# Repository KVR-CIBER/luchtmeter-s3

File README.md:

# Luchtmeter S3 (v2.0)

By **Kobe Vanrobaeys** ([@KVR-CIBER](https://github.com/KVR-CIBER)) and co-inventor **[@varol56](https://github.com/varol56)**.

ESP32-S3 air-quality meter behind a **4.3" 800x480 IPS capacitive touchscreen**, LiPo battery, deep sleep, NFC tag and
Home Assistant (ESPHome). The front is only the screen, a small light window and the NFC spot; every part sits on the back.

| Block | Part |
|---|---|
| Brain | **ESP32-S3-WROOM-1U-N16R8**: external 2.4 GHz antenna (U.FL) at the top of the case, the best WiFi possible |
| Screen | **Waveshare 4.3inch Capacitive Touch LCD** (art. 16249, IPS 800x480, GT911): screwed (M2) onto its own 4.1 mm standoffs; 40-pin FFC to J1 |
| CO2 | Sensirion **SCD41** (photoacoustic, 400-5000 ppm), behind the back vents |
| Temperature / humidity | Sensirion **SHT45** (+-0.1 C) on a slotted, copper-free tongue (no heat from the ESP/charger) |
| Light | **LTR-303ALS** on the front, behind a light pipe in the case |
| NFC | **ST25DV04K** + 8-turn antenna coil on the board (3.5 uH + 10 pF). A phone tap can wake the meter (GPO -> IO16) |
| Charging | TI **BQ24075**, ~250 mA for the 300 mAh LiPo (R5 3.6k), power path: works while charging. Red LED = charging, green = USB |
| Battery | LiPo soldered to **BAT+ / BAT-**, extra DW01A protection |
| 3.3 V / 5 V | XC6220 LDO (8 uA) / TPS61023 boost for the screen (off in deep sleep) |
| Test points | **TP1-TP13** on the back, 1.5 mm pads in one row with the net name in silkscreen: GND, VBUS, VBAT, VSYS, 3V3, 3V3_SW, V5D, TP_3V3, SDA0, SCL0, SDA1, SCL1, GND (issue #1) |
| Probe connector | **J3** (1x4, 2.54 mm, not assembled) at the left edge next to the USB-C: GND / 3V3 / SDA1 / SCL1 (Qwiic order) on the second I2C bus, for an external SHT4x probe (issue #2). 3V3 = TP_3V3, the screen's 3.3 V, the same rail as the I2C1 pull-ups |

Board 106 x 88 mm, 4 layers, notch on the right for the screen's 2x20 header. Checks: **DRC 0, unconnected 0, ERC 0, parity 0**.
(All routed by the tools: Freerouting + `tools/finisher.py`. Freerouting runs multithreaded and is not deterministic;
if `build_all.sh` ends with open connections, run it again.)

## Check before ordering
1. **FFC cable** between the screen (H1) and J1: J1 is turned so pin 1 is on the same side as on the screen; the cable makes
   a U-fold. Check with the cable that comes with the screen (same-side or opposite-side contacts) before soldering.
2. **NFC tuning**: C23 = 10 pF is calculated; the best value can be 8-15 pF (test with the ST "NFC Tap" app).

## Probe on J3 (issue #2)
J3 is on the touch bus (I2C1, GPIO7/8, GT911 at 0x5D) and not on the sensor bus, because an SHT45 probe has the same fixed
address (0x44) as U6. Its 3V3 pin is the screen's own 3.3 V (TP_3V3), so the probe is only powered while the screen is on,
and a powered-down probe is never fed through SDA/SCL. Solder the 4 wires straight onto J3 (a standard 8.5 mm header would
touch the back plate) and lay the cable into the notch in the left wall of the case. Firmware: uncomment the `sht4x`
block on `bus_touch` in `firmware/luchtmeter.yaml`.

## Case (`case/`)
`build_case.py` (CadQuery) -> `case/out/`: `luchtmeter_voorkant.stl` (print face-down), `luchtmeter_achterplaat.stl`,
`luchtmeter_standaard.stl` (desk stand, 20 deg), STEP files, and photo renders (`foto_*.png`, KiCad raytracer).
111.6 x 93.6 x 25.6 mm. 2x M3 x 12 self-tapping screws hold back plate + PCB; 4x M2 x 5 screws hold the PCB to the screen.
The left wall has the USB-C opening and a 5 mm cable notch for the probe on J3 (`render_linkerwand.png`). `render.py`
(trimesh + matplotlib + networkx) makes the shaded case renders.

## Firmware
`firmware/luchtmeter.yaml` (ESPHome, not yet tested on hardware; `esphome config` + `esphome compile` ok with ESPHome
2026.10.0): RGB565 screen (rpi_dpi_rgb), GT911 touch, SCD41 single-shot, SHT45, LTR-303, battery %, deep sleep 5 min,
wake on WEKKEN button or NFC tap. Before 3V3_SW (GPIO15) or the screen (GPIO17) goes off, the SDA/SCL pins of that bus
(GPIO4/5, GPIO7/8) become inputs without pull-up, so the ESP32 never feeds the powered-down chips through its I/O pins;
the ESP32's internal I2C pull-ups are off (the 4k7 pull-ups on the board are on the switched rails). Optional: external
SHT4x probe on J3 (commented out). Needs a `firmware/secrets.yaml` with `wifi_ssid` / `wifi_password`.

## Files
`tools/design.py` = single source of truth; `tools/build_all.sh` rebuilds everything. JLC files in `fab/`.

## Build environment
The board files are **KiCad 10**. Tool paths come from `tools/env.sh` / `tools/kienv.py`: on macOS the defaults are
KiCad.app and brew's openjdk, anything can be overridden with `KICAD_PY`, `KICAD_CLI`, `KICAD_SHARE`, `VENV_PY`, `JAVA`.

Linux (tested on Debian 13 trixie, which only ships KiCad 9):
```sh
apt install flatpak openjdk-25-jre-headless python3-venv          # freerouting 2.4.1 needs Java 25
flatpak remote-add --if-not-exists flathub https://dl.flathub.org/repo/flathub.flatpakrepo
flatpak install flathub org.kicad.KiCad                            # KiCad 10; tools/flatpak/ wraps kicad-cli + its python
# default global library tables (normally made on the first GUI start; without them ERC warns about 'power')
flatpak run --command=sh org.kicad.KiCad -c 'cp -n /app/extensions/Library/template/*-lib-table $XDG_CONFIG_HOME/kicad/10.0/'
python3 -m venv .venv && .venv/bin/pip install numpy shapely matplotlib cadquery trimesh networkx
python3 -m venv .venv-esphome && .venv-esphome/bin/pip install esphome
tools/build_all.sh                                                 # board + schematic + routing + checks + fab/
.venv/bin/python case/build_case.py && .venv/bin/python case/render.py
cd firmware && ../.venv-esphome/bin/esphome compile luchtmeter.yaml
```
The flatpak sandbox has its own `/tmp`: give kicad-cli output paths inside the repo.

## Authors
- Kobe Vanrobaeys ([@KVR-CIBER](https://github.com/KVR-CIBER))
- [@varol56](https://github.com/varol56), co-inventor

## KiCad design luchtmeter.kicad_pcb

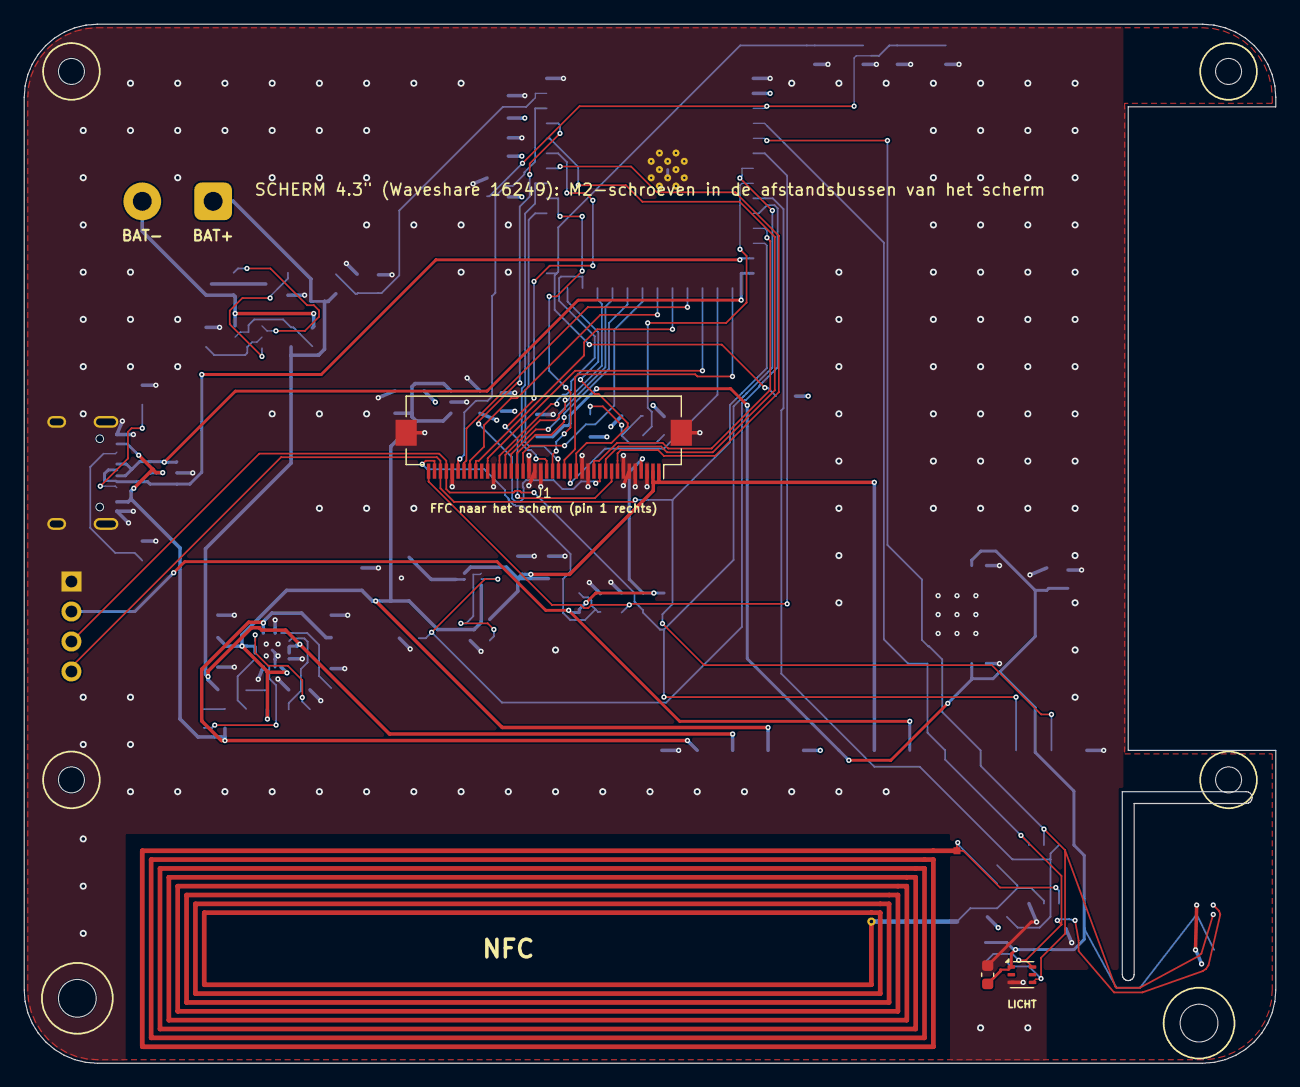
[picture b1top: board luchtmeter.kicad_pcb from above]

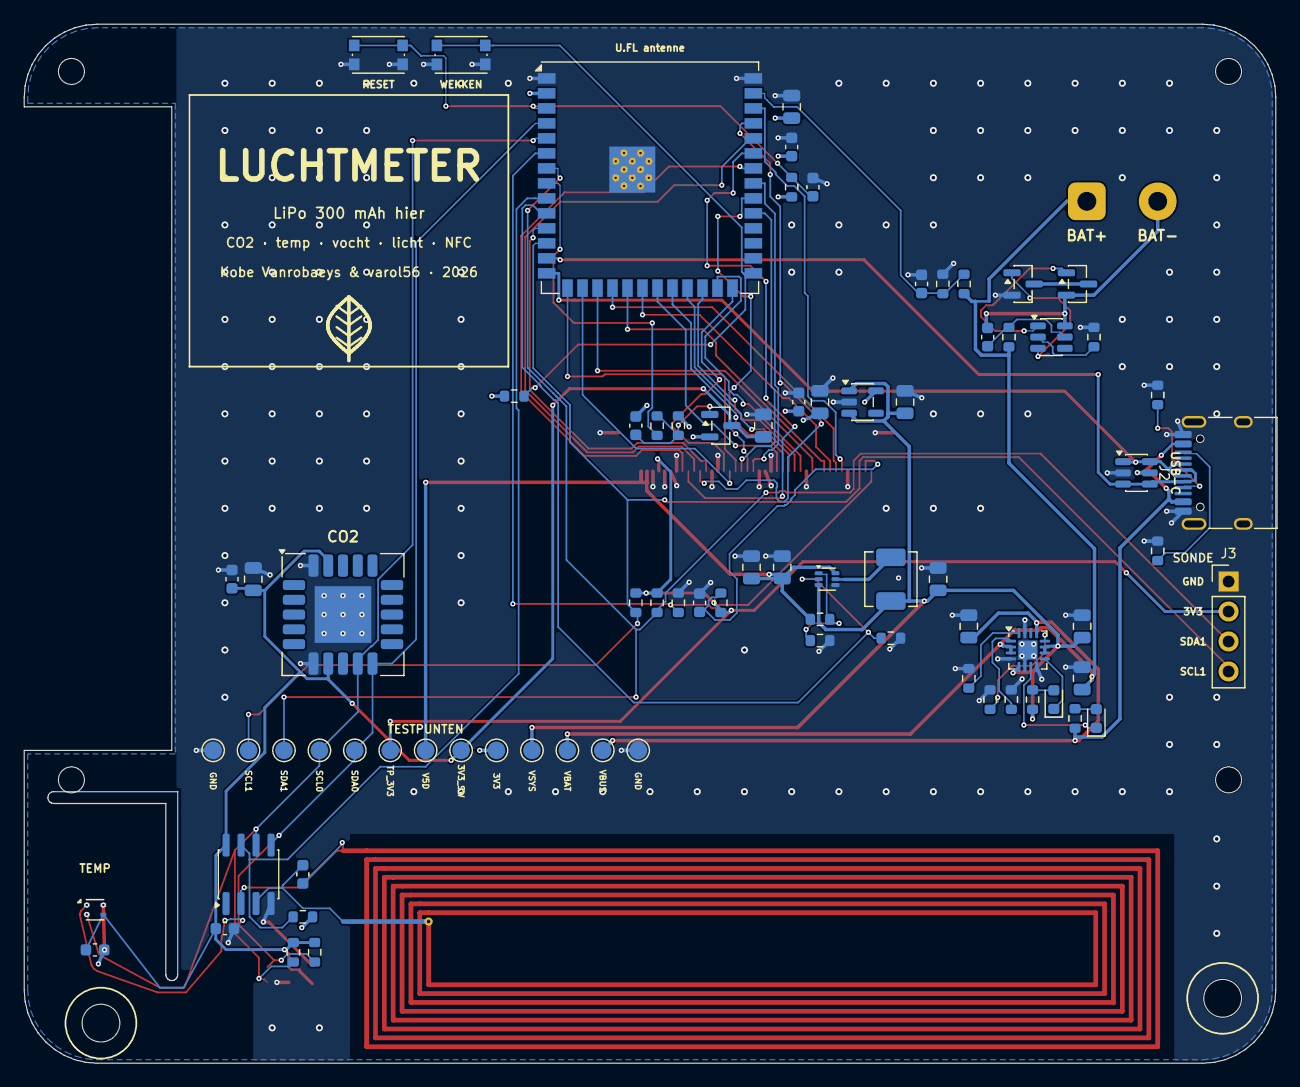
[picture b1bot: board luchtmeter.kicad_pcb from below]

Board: 4 copper layers, 106.0 x 88.0 mm, 90 parts (80 on the bottom side), 63 nets.

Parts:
ANT1: NFC antenne; NFC_Coil
C1, C10, C15, C16: 22u; C_0805_2012Metric
C2, C7, C8, C11, C18, C20, C21, C22: 100n; C_0603_1608Metric
C3, C17: 1u; C_0603_1608Metric
C4, C6: 4u7; C_0805_2012Metric
C5, C9, C13, C14, C19: 10u; C_0805_2012Metric
C12: 47n; C_0603_1608Metric
C23: 10p; C_0603_1608Metric
D1: rood laden; LED_0603_1608Metric
D2: groen USB; LED_0603_1608Metric
H1, H2, H3, H4: M2; MountingHole_2.2mm_M2
H5, H6: M3; MountingHole_3.2mm_M3
J1: SCHERM; Hirose_FH12-40S-0.5SH_1x40-1MP_P0.50mm_Horizontal
J2: USB-C; USB_C_Receptacle_HRO_TYPE-C-31-M-12
J3: SONDE I2C1; PinHeader_1x04_P2.54mm_Vertical
J4: BATTERIJ; SolderWire_2pad_P6mm_D1.6mm_BAT
L1: 1uH; L_Sunlord_MWSA0402S
Q2: AO3401A; SOT-23
Q3, Q4: AO3400A; SOT-23
R1, R2, R7, R15, R19, R20: 10k; R_0603_1608Metric
R3, R4: 5k1; R_0603_1608Metric
R5: 3.6k; R_0603_1608Metric
R6: 1.1k; R_0603_1608Metric
R8, R9, R11: 1k; R_0603_1608Metric
R10: 100; R_0603_1608Metric
R12, R13: 1M; R_0603_1608Metric
R14, R17, R18, R25: 100k; R_0603_1608Metric
R16: 732k; R_0603_1608Metric
R21, R22, R23, R24: 4k7; R_0603_1608Metric
SW1: WEKKEN; SW_Push_1P1T_NO_CK_KMR2
SW2: RESET; SW_Push_1P1T_NO_CK_KMR2
TP1, TP13: GND; TestPoint_Pad_D1.5mm
TP2: VBUS; TestPoint_Pad_D1.5mm
TP3: VBAT; TestPoint_Pad_D1.5mm
TP4: VSYS; TestPoint_Pad_D1.5mm
TP5: 3V3; TestPoint_Pad_D1.5mm
TP6: 3V3_SW; TestPoint_Pad_D1.5mm
TP7: V5D; TestPoint_Pad_D1.5mm
TP8: TP_3V3; TestPoint_Pad_D1.5mm
TP9: SDA0; TestPoint_Pad_D1.5mm
TP10: SCL0; TestPoint_Pad_D1.5mm
TP11: SDA1; TestPoint_Pad_D1.5mm
TP12: SCL1; TestPoint_Pad_D1.5mm
U1: ESP32-S3-WROOM-1U-N16R8; ESP32-S3-WROOM-1U
U2: USBLC6-2SC6; SOT-23-6
U3: XC6220B331MR; SOT-23-5
U4: LTR-303ALS-01; Lite-On_LTR-303ALS-01
U5: SCD41-D-R2; Sensirion_SCD4x-1EP_10.1x10.1mm_P1.25mm_EP4.8x4.8mm
U6: SHT45; Sensirion_DFN-4_1.5x1.5mm_P0.8mm_SHT4x_NoCentralPad
U7: BQ24075; VQFN-16-1EP_3x3mm_P0.5mm_EP1.6x1.6mm
U8: DW01A; SOT-23-6
U9: TPS61023; SOT-563
U10: ST25DV04K; SOIC-8_3.9x4.9mm_P1.27mm

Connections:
3V3: C1.1, C2.1, C10.1, C11.1, C12.2, Q2.2, R1.1, R2.1, R14.2, R25.2, TP5.1, U1.2, U3.5
3V3_SW: C13.1, C18.1, C19.1, C20.1, C21.1, C22.1, Q2.3, R23.2, R24.2, TP6.1, U4.1, U5.7, U5.19, U6.3, U10.8
BATN: C7.2, J4.2, Q3.2, U8.6
BAT_MID: Q3.3, Q4.3
BL_PWM: J1.35, U1.38
BST_FB: R16.2, R17.1, U9.1
BST_SW: L1.2, U9.5
CC1: J2.A5, R3.1
CC2: J2.B5, R4.1
CHG: D1.1, U7.9
CH_ILIM: R6.1, U7.12
CH_ISET: R5.1, U7.16
CH_TS: R7.1, U7.1
DE: J1.34, U1.18
DISP_ON: R18.1, U1.10, U9.2
DW_CS: R11.1, U8.2
DW_OC: Q4.1, U8.3
DW_OD: Q3.1, U8.1
DW_VCC: C7.1, R10.2, U8.5
ESP_EN: C3.1, R1.2, SW2.1, U1.3
ESP_IO0: R2.2, SW1.1, U1.27
GND: C1.2, C2.2, C3.2, C4.2, C5.2, C6.2, C8.2, C9.2, C10.2, C11.2, C13.2, C14.2, C15.2, C16.2, C17.2, C18.2, C19.2, C20.2, C21.2, C22.2, J1.3, J1.5, J1.6, J1.7, J1.13, J1.14, J1.21, J1.22, J1.23, J1.29, J1.36, J1.MP, J2.A1, J2.A12, J2.B1, J2.B12, J2.SH, J3.1, Q4.2, R3.2, R4.2, R5.2, R6.2, R7.2, R11.2, R13.2, R17.2, R18.2, R20.2, SW1.2, SW2.2, TP1.1, TP13.1, U1.1, U1.40, U1.41, U2.2, U3.2, U4.3, U5.6, U5.20, U5.21, U6.4, U7.4, U7.6, U7.8, U7.15, U7.17, U9.4, U10.4
HSYNC: J1.32, U1.19
LCD_B3: J1.24, U1.21
LCD_B4: J1.25, U1.22
LCD_B5: J1.26, U1.23
LCD_B6: J1.27, U1.24
LCD_B7: J1.28, U1.25
LCD_G2: J1.15, U1.26
LCD_G3: J1.16, U1.16
LCD_G4: J1.17, U1.15
LCD_G5: J1.18, U1.31
LCD_G6: J1.19, U1.32
LCD_G7: J1.20, U1.33
LCD_R3: J1.8, U1.34
LCD_R4: J1.9, U1.35
LCD_R5: J1.10, U1.36
LCD_R6: J1.11, U1.37
LCD_R7: J1.12, U1.11
LED_CHG_A: D1.2, R8.2
LED_PG_A: D2.2, R9.2
NFC_AC0: ANT1.1, C23.1, U10.2
NFC_AC1: ANT1.2, C23.2, U10.3
NFC_GPO: R25.1, U1.9, U10.7
PCLK: J1.30, U1.17
PGOOD: D2.1, U7.7
PWR_EN: R15.1, U1.8
PWR_G: C12.1, Q2.1, R14.1, R15.2
SCL0: R24.1, TP10.1, U1.5, U4.4, U5.9, U6.2, U10.6
SCL1: J1.38, J3.4, R22.1, TP12.1, U1.12
SDA0: R23.1, TP9.1, U1.4, U4.6, U5.10, U6.1, U10.5
SDA1: J1.37, J3.3, R21.1, TP11.1, U1.7
TP_3V3: J1.4, J3.2, R19.1, R21.2, R22.2, TP8.1
TP_INT: J1.40, R20.1, U1.6
TP_RST: C17.1, J1.39, R19.2
USB_DM: J2.A7, J2.B7, U1.13, U2.3, U2.4
USB_DP: J2.A6, J2.B6, U1.14, U2.1, U2.6
V5D: C15.1, C16.1, J1.1, J1.2, R16.1, TP7.1, U9.6
VBAT: C6.1, J4.1, R10.1, R12.1, TP3.1, U7.2, U7.3
VBAT_SENSE: C8.1, R12.2, R13.1, U1.39
VBUS: C4.1, J2.A4, J2.A9, J2.B4, J2.B9, R9.1, TP2.1, U2.5, U7.13
VSYNC: J1.33, U1.20
VSYS: C5.1, C9.1, C14.1, L1.1, R8.1, TP4.1, U3.1, U3.3, U7.5, U7.10, U7.11, U9.3

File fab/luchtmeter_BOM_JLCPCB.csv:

Comment,Designator,Footprint,Quantity,MPN / note,LCSC Part #
ESP32-S3-WROOM-1U-N16R8,U1,ESP32-S3-WROOM-1U,1,ESP32-S3-WROOM-1U-N16R8 (U.FL; use a 2.4 GHz flex/dipole antenna at the top of the case),C3013946
22u,"C1,C10,C15,C16",C_0805_2012Metric,4,0805 22u X5R ceramic,C29277
100n,"C2,C7,C8,C11,C18,C20,C21,C22",C_0603_1608Metric,8,0603 100n X7R ceramic,C14663
10k,"R1,R2,R15",R_0603_1608Metric,3,0603 10k 1%,C25804
1u,"C3,C17",C_0603_1608Metric,2,0603 1u X5R ceramic,C15849
WEKKEN,SW1,SW_Push_1P1T_NO_CK_KMR2,1,CK KMR221G: wake from deep sleep (= BOOT when held at reset),C72443
RESET,SW2,SW_Push_1P1T_NO_CK_KMR2,1,CK KMR221G,C72443
USB-C,J2,USB_C_Receptacle_HRO_TYPE-C-31-M-12,1,HRO TYPE-C-31-M-12,C165948
5k1,"R3,R4",R_0603_1608Metric,2,0603 5k1 1%,C23186
USBLC6-2SC6,U2,SOT-23-6,1,USBLC6-2SC6,C2687116
BQ24075,U7,VQFN-16-1EP_3x3mm_P0.5mm_EP1.6x1.6mm,1,TI BQ24075RGTR (Li-ion charger + power path),C15464
4u7,"C4,C6",C_0805_2012Metric,2,0805 4u7 X5R ceramic,C132173
10u,"C5,C9,C13,C14,C19",C_0805_2012Metric,5,0805 10u X5R ceramic,C15850
3.6k,R5,R_0603_1608Metric,1,0603 3.6k 1% (charge ~250 mA; 1k = 0.9 A),C22980
1.1k,R6,R_0603_1608Metric,1,0603 1.1k 1% (input limit ~1.4 A),C22764
10k,R7,R_0603_1608Metric,1,"0603 10k 1% (TS: fixed 10k, no NTC)",C25804
1k,"R8,R9,R11",R_0603_1608Metric,3,0603 1k 1%,C21190
rood laden,D1,LED_0603_1608Metric,1,LED 0603 red (charging),C2286
groen USB,D2,LED_0603_1608Metric,1,LED 0603 green (USB power),C12624
BATTERIJ,J4,SolderWire_2pad_P6mm_D1.6mm_BAT,1,solder pads for the LiPo leads,"(solder pads, no part)"
DW01A,U8,SOT-23-6,1,DW01A (Li-ion protection),C351410
100,R10,R_0603_1608Metric,1,0603 100 1%,C22775
AO3400A,Q3,SOT-23,1,AO3400A (discharge FET),C20917
AO3400A,Q4,SOT-23,1,AO3400A (charge FET),C20917
1M,R12,R_0603_1608Metric,1,0603 1M 1% (battery voltage / 2),C22935
1M,R13,R_0603_1608Metric,1,0603 1M 1%,C22935
XC6220B331MR,U3,SOT-23-5,1,Torex XC6220B331MR-G,C86534
AO3401A,Q2,SOT-23,1,AO3401A (load switch: sensors + NFC),C15127
100k,"R14,R17,R25",R_0603_1608Metric,3,0603 100k 1%,C25803
47n,C12,C_0603_1608Metric,1,0603 47n X7R ceramic,C107093
TPS61023,U9,SOT-563,1,"TI TPS61023DRLR (3.7 A boost, 0.1 uA shutdown)",C919459
1uH,L1,L_Sunlord_MWSA0402S,1,Sunlord MWSA0402S-1R0MT (1 uH),C408332
732k,R16,R_0603_1608Metric,1,0603 732k 1%,C23239
100k,R18,R_0603_1608Metric,1,0603 100k (screen off at boot / in sleep),C25803
SCHERM,J1,Hirose_FH12-40S-0.5SH_1x40-1MP_P0.50mm_Horizontal,1,Hirose FH12-40S-0.5SH(55): 40-pin 0.5 mm FFC to the Waveshare 4.3in Capacitive Touch LCD (RGB cable interface),C202114
10k,R19,R_0603_1608Metric,1,0603 10k (GT911 power-on reset),C25804
10k,R20,R_0603_1608Metric,1,0603 10k (INT low at reset -> GT911 address 0x5D),C25804
4k7,"R21,R22,R23,R24",R_0603_1608Metric,4,0603 4k7 1%,C23162
LTR-303ALS-01,U4,Lite-On_LTR-303ALS-01,1,"LTR-303ALS-01 (ambient light, front window)",C364577
SCD41-D-R2,U5,Sensirion_SCD4x-1EP_10.1x10.1mm_P1.25mm_EP4.8x4.8mm,1,"Sensirion SCD41-D-R2 (CO2 400-5000 ppm + RH/T), behind the back vents",C3659294
SHT45,U6,Sensirion_DFN-4_1.5x1.5mm_P0.8mm_SHT4x_NoCentralPad,1,Sensirion SHT45-AD1B-R2 (+-0.1 C),C5221601
ST25DV04K,U10,SOIC-8_3.9x4.9mm_P1.27mm,1,"ST ST25DV04K-IER6S3 (dynamic NFC tag, I2C)",C155601
NFC antenne,ANT1,NFC_Coil,1,"PCB loop antenna (copper on the board, no part)","(PCB copper, no part)"
10p,C23,C_0603_1608Metric,1,0603 10p C0G (3.5 uH coil + 28.5 pF internal + 10 pF = 13.6 MHz; tune 8-15 pF),C1634

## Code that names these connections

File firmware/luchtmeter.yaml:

# Luchtmeter S3 v2 - ESPHome firmware for Home Assistant (first version, NOT yet tested on hardware)
# Authors: Kobe Vanrobaeys (@KVR-CIBER) & varol56 (@varol56, co-inventor)
# Screen: Waveshare 4.3in Capacitive Touch LCD (800x480 RGB565 + GT911). Sensors: SCD41, SHT45, LTR-303. NFC: ST25DV04K.
# Battery: wakes every 5 min (or on the WEKKEN button / an NFC tap), measures, sends to Home Assistant, sleeps again.

substitutions:
  name: luchtmeter
  sleep_time: 5min
  awake_time: 45s

esphome:
  name: ${name}
  friendly_name: Luchtmeter
  platformio_options:
    board_build.flash_mode: dio
  on_boot:
    - priority: 1100                           # before the I2C buses are set up (priority 1000)
      then:
        - lambda: |-
            // the I2C pins were held as floating inputs through deep sleep (release_*_bus): give them back
            for (gpio_num_t p : {GPIO_NUM_4, GPIO_NUM_5, GPIO_NUM_7, GPIO_NUM_8}) gpio_hold_dis(p);
    - priority: 900
      then:
        - switch.turn_on: sensor_power         # 3V3_SW: sensors + NFC
        - switch.turn_on: screen_power         # 5 V boost for the screen
  on_shutdown:                                 # before deep sleep: screen off first, then the sensor rail
    - light.turn_off: backlight
    - switch.turn_off: screen_power
    - switch.turn_off: sensor_power

esp32:
  board: esp32-s3-devkitc-1
  variant: esp32s3
  flash_size: 16MB
  framework:
    type: esp-idf

psram:
  mode: octal
  speed: 80MHz

wifi:                                          # WROOM-1U + external antenna at the top of the case
  ssid: !secret wifi_ssid
  password: !secret wifi_password
  fast_connect: true

api:
ota:
  - platform: esphome
logger:

# ---------------------------------------------------------------- power + sleep
# Issue #2 (varol56): the I2C pull-ups sit on the switched rails (bus_sensors: 3V3_SW, bus_touch: TP_3V3 = the screen's own
# 3.3 V). Before a rail goes off, its SDA/SCL pins become inputs without pull-up, otherwise the ESP32 feeds the powered-down
# chips through the I/O pins (back-powering: costs current and can hang the bus). Always switch the rails with
# sensor_power / screen_power (never pwr_en / disp_on directly). The rails only go off before deep sleep; waking up is a
# reboot, so the buses are set up again from scratch.
switch:
  - platform: gpio
    id: pwr_en
    pin: {number: GPIO15, inverted: true}      # PWR_EN low = 3V3_SW on
    restore_mode: ALWAYS_ON
    internal: true
  - platform: gpio
    id: disp_on
    pin: GPIO17                                # DISP_ON: TPS61023 enable (5 V for the screen -> its TP_3V3 for the touch)
    restore_mode: ALWAYS_ON
    internal: true
  - platform: template
    id: sensor_power
    internal: true
    lambda: return id(pwr_en).state;
    turn_on_action:
      - switch.turn_on: pwr_en
    turn_off_action:
      - script.execute: release_sensor_bus     # GPIO4/5 floating first ...
      - switch.turn_off: pwr_en                # ... then 3V3_SW off
  - platform: template
    id: screen_power
    internal: true
    lambda: return id(disp_on).state;
    turn_on_action:
      - switch.turn_on: disp_on
    turn_off_action:
      - script.execute: release_touch_bus      # GPIO7/8 floating first ...
      - switch.turn_off: disp_on               # ... then the screen (and TP_3V3, the probe on J3) off

script:
  - id: release_sensor_bus
    then:
      - lambda: |-
          for (gpio_num_t p : {GPIO_NUM_4, GPIO_NUM_5}) {      // SDA0, SCL0
            gpio_set_direction(p, GPIO_MODE_INPUT);             // no output driver (also detaches the I2C peripheral)
            gpio_set_pull_mode(p, GPIO_FLOATING);               // no internal pull-up / pull-down
            gpio_hold_en(p);                                    // keep it like this through deep sleep (on_boot releases)
          }
  - id: release_touch_bus
    then:
      - lambda: |-
          for (gpio_num_t p : {GPIO_NUM_7, GPIO_NUM_8}) {      // SDA1, SCL1 (GT911 + the probe on J3)
            gpio_set_direction(p, GPIO_MODE_INPUT);
            gpio_set_pull_mode(p, GPIO_FLOATING);
            gpio_hold_en(p);
          }

deep_sleep:
  id: sleeper
  run_duration: ${awake_time}
  sleep_duration: ${sleep_time}
  esp32_ext1_wakeup:                           # WEKKEN button (IO0) or a phone tapping the NFC tag (ST25DV GPO, IO16)
    pins: [GPIO0, GPIO16]
    mode: ANY_LOW

sensor:
  - platform: adc
    id: vbat
    name: "Batterij spanning"
    pin: GPIO1
    attenuation: 12db
    filters:
      - multiply: 2.0                          # 1M / 1M divider
    update_interval: 30s
  - platform: template
    name: "Batterij"
    unit_of_measurement: "%"
    device_class: battery
    lambda: |-
      return clamp((id(vbat).state - 3.3f) / (4.15f - 3.3f) * 100.0f, 0.0f, 100.0f);
    update_interval: 30s
  - platform: scd4x
    i2c_id: bus_sensors
    measurement_mode: single_shot
    co2:
      id: co2
      name: "CO2"
    update_interval: 30s
  - platform: sht4x
    i2c_id: bus_sensors
    temperature:
      id: temp
      name: "Temperatuur"
    humidity:
      id: hum
      name: "Vochtigheid"
    update_interval: 30s
  - platform: ltr_als_ps
    i2c_id: bus_sensors
    type: ALS
    ambient_light:
      id: lux
      name: "Licht"
    update_interval: 30s
  # Optional (issue #2): external SHT4x probe on connector J3 (GND / 3V3 / SDA1 / SCL1, e.g. the long greenhouse soil probe)
  # for tests or calibration. It sits on bus_touch because it has the same fixed address 0x44 as the SHT45 on the board.
  # J3's 3V3 is TP_3V3 (the screen's 3.3 V), so the probe is only powered while the screen is on. Uncomment to use:
  # - platform: sht4x
  #   i2c_id: bus_touch
  #   address: 0x44
  #   temperature:
  #     id: probe_temp
  #     name: "Sonde temperatuur"
  #   humidity:
  #     id: probe_hum
  #     name: "Sonde vochtigheid"
  #   update_interval: 30s

i2c:
  # 4k7 pull-ups on the board, to the switched rails: the ESP32's internal pull-ups (always-on 3.3 V) must stay off,
  # or they would back-power the sensors / touch through SDA/SCL while those rails are off.
  - id: bus_sensors                            # SCD41 0x62, SHT45 0x44, LTR-303 0x29, ST25DV 0x53/0x57/0x2D
    sda: GPIO4
    scl: GPIO5
    sda_pullup_enabled: false
    scl_pullup_enabled: false
  - id: bus_touch                              # GT911 0x5D (+ optional probe on J3)
    sda: GPIO7
    scl: GPIO8
    sda_pullup_enabled: false
    scl_pullup_enabled: false

# ---------------------------------------------------------------- screen + touch
output:
  - platform: ledc
    id: bl_pwm
    pin: GPIO2                                 # PWM pin of the screen (backlight boost)

light:
  - platform: monochromatic
    id: backlight
    name: "Scherm helderheid"
    output: bl_pwm
    restore_mode: ALWAYS_ON

font:
  - file: "gfonts://Inter@700"
    id: big
    size: 140
  - file: "gfonts://Inter@500"
    id: mid
    size: 40
  - file: "gfonts://Inter@400"
    id: small
    size: 26

color:
  - {id: groen, hex: "2ecc71"}
  - {id: oranje, hex: "f39c12"}
  - {id: rood, hex: "e74c3c"}
  - {id: grijs, hex: "9aa0a6"}

display:
  - platform: rpi_dpi_rgb                      # 16-bit RGB565 on the ESP32-S3 LCD peripheral
    id: scherm
    dimensions: {width: 800, height: 480}
    color_order: RGB
    pclk_frequency: 16MHz
    de_pin: GPIO10
    pclk_pin: GPIO9
    hsync_pin: GPIO11
    vsync_pin: GPIO12
    hsync_pulse_width: 4
    hsync_back_porch: 8
    hsync_front_porch: 8
    vsync_pulse_width: 4
    vsync_back_porch: 8
    vsync_front_porch: 8
    data_pins:
      red: [GPIO41, GPIO42, GPIO44, GPIO43, GPIO18]
      green: [GPIO45, GPIO46, GPIO3, GPIO38, GPIO39, GPIO40]
      blue: [GPIO13, GPIO14, GPIO21, GPIO47, GPIO48]
    update_interval: 5s
    lambda: |-
      float c = id(co2).has_state() ? id(co2).state : 0;
      Color kl = c < 800 ? id(groen) : (c < 1200 ? id(oranje) : id(rood));
      it.fill(Color::BLACK);
      it.print(400, 40, id(mid), id(grijs), TextAlign::TOP_CENTER, "CO2  ppm");
      it.printf(400, 200, id(big), kl, TextAlign::CENTER, "%.0f", c);
      it.printf(130, 380, id(mid), Color::WHITE, TextAlign::CENTER, "%.1f °C", id(temp).state);
      it.printf(400, 380, id(mid), Color::WHITE, TextAlign::CENTER, "%.0f %%", id(hum).state);
      it.printf(670, 380, id(mid), Color::WHITE, TextAlign::CENTER, "%.0f lux", id(lux).state);
      it.printf(780, 450, id(small), id(grijs), TextAlign::BOTTOM_RIGHT, "%.2f V", id(vbat).state);

touchscreen:
  - platform: gt911
    i2c_id: bus_touch
    interrupt_pin: GPIO6
    on_touch:
      - deep_sleep.prevent: sleeper            # touching keeps it awake for 30 s
      - delay: 30s
      - deep_sleep.allow: sleeper
